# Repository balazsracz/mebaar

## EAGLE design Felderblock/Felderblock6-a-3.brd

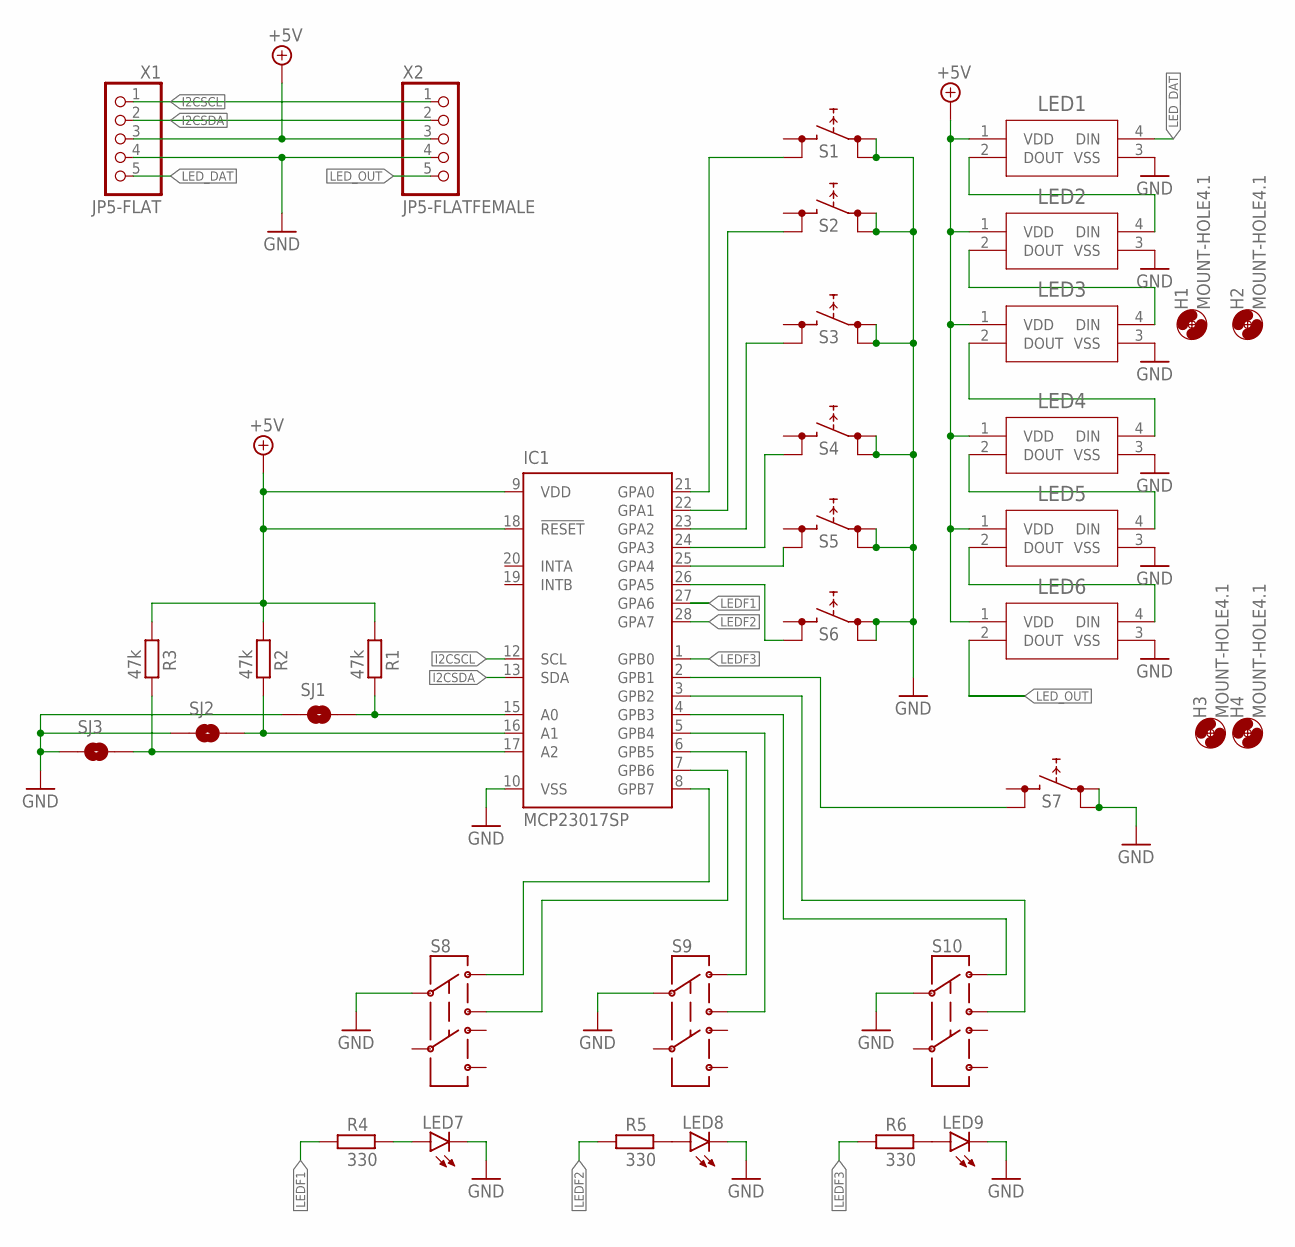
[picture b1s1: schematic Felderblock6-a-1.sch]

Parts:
H1, H2, H3, H4: MOUNT-HOLE4.1; 4,1
IC1: MCP23017SP; DIL28-3
LED1, LED2, LED3, LED4, LED5, LED6: LED-2812BCOM-16347_SPK-M; COM-16347_SPK-M
LED7, LED8, LED9: LEDCHIPLED_0805; CHIPLED_0805
R1, R2, R3: 47k; R0805
R4, R5, R6: 330; R0805
S1, S2, S3, S4, S5, S6, S7: W1; TACTSW-6X6
S8, S9, S10: SWITCH-DPDT; DP-T1
SJ1, SJ2, SJ3: SJRND2; SJ_RND2
X1: JP5-FLAT; JP5F
X2: JP5-FLATFEMALE; JP5F-FEM

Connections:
+5V: IC1.9 (VDD), IC1.18 (!RESET), LED1.1 (VDD), LED2.1 (VDD), LED3.1 (VDD), LED4.1 (VDD), LED5.1 (VDD), LED6.1 (VDD), R1.1, R2.1, R3.1, X1.3, X2.3; also elsewhere on the board
GND: IC1.10 (VSS), LED1.3 (VSS), LED2.3 (VSS), LED3.3 (VSS), LED4.3 (VSS), LED5.3 (VSS), LED6.3 (VSS), LED7.C, LED8.C, LED9.C, S1.1 (1.1), S1.2 (1.2), S2.1 (1.1), S2.2 (1.2), S3.1 (1.1), S3.2 (1.2), S4.1 (1.1), S4.2 (1.2), S5.1 (1.1), S5.2 (1.2), S6.1 (1.1), S6.2 (1.2), S7.1 (1.1), S7.2 (1.2), S8.2 (1C), S9.2 (1C), S10.2 (1C), SJ1.P$1 (1), SJ2.P$1 (1), SJ3.P$1 (1), X1.4, X2.4; also elsewhere on the board
I2CSCL: IC1.12 (SCL), X1.1, X2.1
I2CSDA: IC1.13 (SDA), X1.2, X2.2
LEDF1: IC1.27 (GPA6), R4.1
LEDF2: IC1.28 (GPA7), R5.1
LEDF3: IC1.1 (GPB0), R6.1
LED_DAT: LED1.4 (DIN), X1.5
LED_OUT: LED6.2 (DOUT), X2.5
unnamed 9: IC1.15 (A0), R1.2, SJ1.P$2 (2); also elsewhere on the board
unnamed 10: IC1.16 (A1), R2.2, SJ2.P$2 (2); also elsewhere on the board
unnamed 11: IC1.17 (A2), R3.2, SJ3.P$2 (2); also elsewhere on the board
unnamed: IC1.21 (GPA0), S1.4 (2.2)
unnamed: IC1.22 (GPA1), S2.4 (2.2)
unnamed: IC1.23 (GPA2), S3.4 (2.2)
unnamed: IC1.24 (GPA3), S4.4 (2.2)
unnamed: IC1.25 (GPA4), S5.4 (2.2)
unnamed: IC1.26 (GPA5), S6.4 (2.2)
unnamed: IC1.8 (GPB7), S8.1 (1A)
unnamed: IC1.7 (GPB6), S8.3 (1B)
unnamed: LED1.2 (DOUT), LED2.4 (DIN)
unnamed: LED2.2 (DOUT), LED3.4 (DIN)
unnamed: LED3.2 (DOUT), LED4.4 (DIN)
unnamed: LED4.2 (DOUT), LED5.4 (DIN)
unnamed: LED5.2 (DOUT), LED6.4 (DIN)
unnamed: IC1.6 (GPB5), S9.1 (1A)
unnamed: IC1.5 (GPB4), S9.3 (1B)
unnamed: IC1.4 (GPB3), S10.1 (1A)
unnamed: IC1.3 (GPB2), S10.3 (1B)
unnamed: LED8.A, R5.2
unnamed: LED7.A, R4.2
unnamed: LED9.A, R6.2
unnamed 32: IC1.2 (GPB1), S7.4 (2.2); also elsewhere on the board

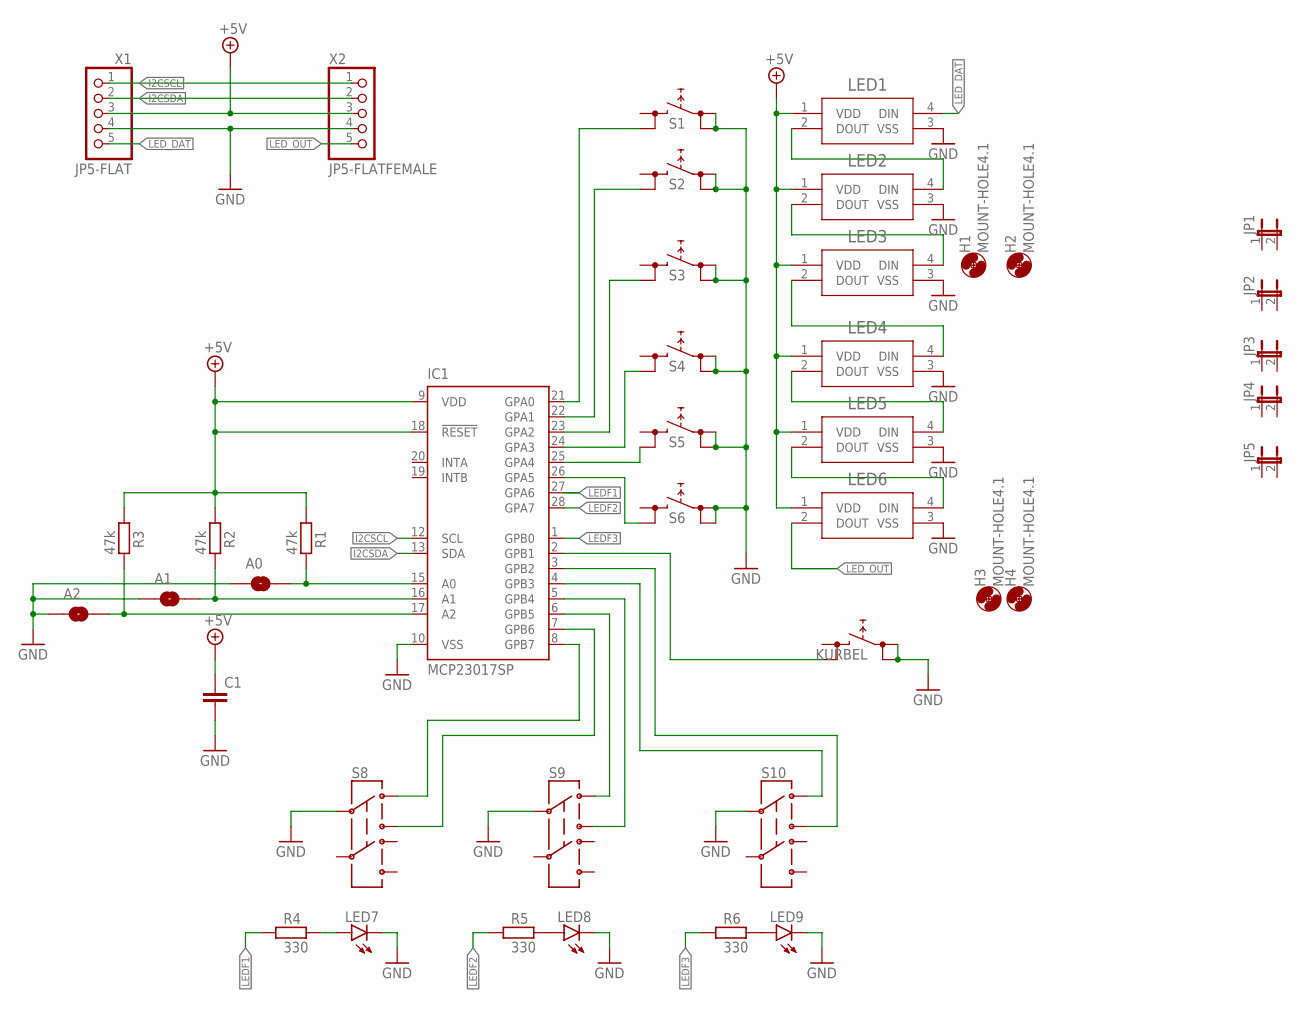
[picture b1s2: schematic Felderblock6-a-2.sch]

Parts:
A0, A1, A2: SJRND2; SJ_RND2
C1: C-EUC0805; C0805
H1, H2, H3, H4: MOUNT-HOLE4.1; 4,1
IC1: MCP23017SP; DIL28-3
JP1, JP2, JP3, JP4, JP5: FELD-BOARD-HOLDER
KURBEL: W1; TACTSW-6X6
LED1, LED2, LED3, LED4, LED5, LED6: LED-2812BCOM-16347_SPK-M; COM-16347_SPK-M
LED7, LED8, LED9: LEDCHIPLED_0805; CHIPLED_0805
R1, R2, R3: 47k; R0805
R4, R5, R6: 330; R0805
S1, S2, S3, S4, S5, S6: W1; TACTSW-6X6
S8, S9, S10: SWITCH-DPDT; DP-T1
X1: JP5-FLAT; JP5F
X2: JP5-FLATFEMALE; JP5F-FEM

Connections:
+5V: C1.1, IC1.9 (VDD), IC1.18 (!RESET), LED1.1 (VDD), LED2.1 (VDD), LED3.1 (VDD), LED4.1 (VDD), LED5.1 (VDD), LED6.1 (VDD), R1.1, R2.1, R3.1, X1.3, X2.3
GND: A0.P$1 (1), A1.P$1 (1), A2.P$1 (1), C1.2, IC1.10 (VSS), KURBEL.1 (1.1), KURBEL.2 (1.2), LED1.3 (VSS), LED2.3 (VSS), LED3.3 (VSS), LED4.3 (VSS), LED5.3 (VSS), LED6.3 (VSS), LED7.C, LED8.C, LED9.C, S1.1 (1.1), S1.2 (1.2), S2.1 (1.1), S2.2 (1.2), S3.1 (1.1), S3.2 (1.2), S4.1 (1.1), S4.2 (1.2), S5.1 (1.1), S5.2 (1.2), S6.1 (1.1), S6.2 (1.2), S8.2 (1C), S9.2 (1C), S10.2 (1C), X1.4, X2.4; also elsewhere on the board
I2CSCL: IC1.12 (SCL), X1.1, X2.1
I2CSDA: IC1.13 (SDA), X1.2, X2.2
LEDF1: IC1.27 (GPA6), R4.1
LEDF2: IC1.28 (GPA7), R5.1
LEDF3: IC1.1 (GPB0), R6.1
LED_DAT: LED1.4 (DIN), X1.5
LED_OUT: LED6.2 (DOUT), X2.5
unnamed 9: A0.P$2 (2), IC1.15 (A0), R1.2; also elsewhere on the board
unnamed 10: A1.P$2 (2), IC1.16 (A1), R2.2; also elsewhere on the board
unnamed 11: A2.P$2 (2), IC1.17 (A2), R3.2; also elsewhere on the board
unnamed: IC1.21 (GPA0), S1.4 (2.2)
unnamed: IC1.22 (GPA1), S2.4 (2.2)
unnamed: IC1.23 (GPA2), S3.4 (2.2)
unnamed: IC1.24 (GPA3), S4.4 (2.2)
unnamed: IC1.25 (GPA4), S5.4 (2.2)
unnamed: IC1.26 (GPA5), S6.4 (2.2)
unnamed: IC1.8 (GPB7), S8.1 (1A)
unnamed: IC1.7 (GPB6), S8.3 (1B)
unnamed: LED1.2 (DOUT), LED2.4 (DIN)
unnamed: LED2.2 (DOUT), LED3.4 (DIN)
unnamed: LED3.2 (DOUT), LED4.4 (DIN)
unnamed: LED4.2 (DOUT), LED5.4 (DIN)
unnamed: LED5.2 (DOUT), LED6.4 (DIN)
unnamed: IC1.6 (GPB5), S9.1 (1A)
unnamed: IC1.5 (GPB4), S9.3 (1B)
unnamed: IC1.4 (GPB3), S10.1 (1A)
unnamed: IC1.3 (GPB2), S10.3 (1B)
unnamed: LED8.A, R5.2
unnamed: LED7.A, R4.2
unnamed: LED9.A, R6.2
unnamed 32: IC1.2 (GPB1), KURBEL.4 (2.2); also elsewhere on the board

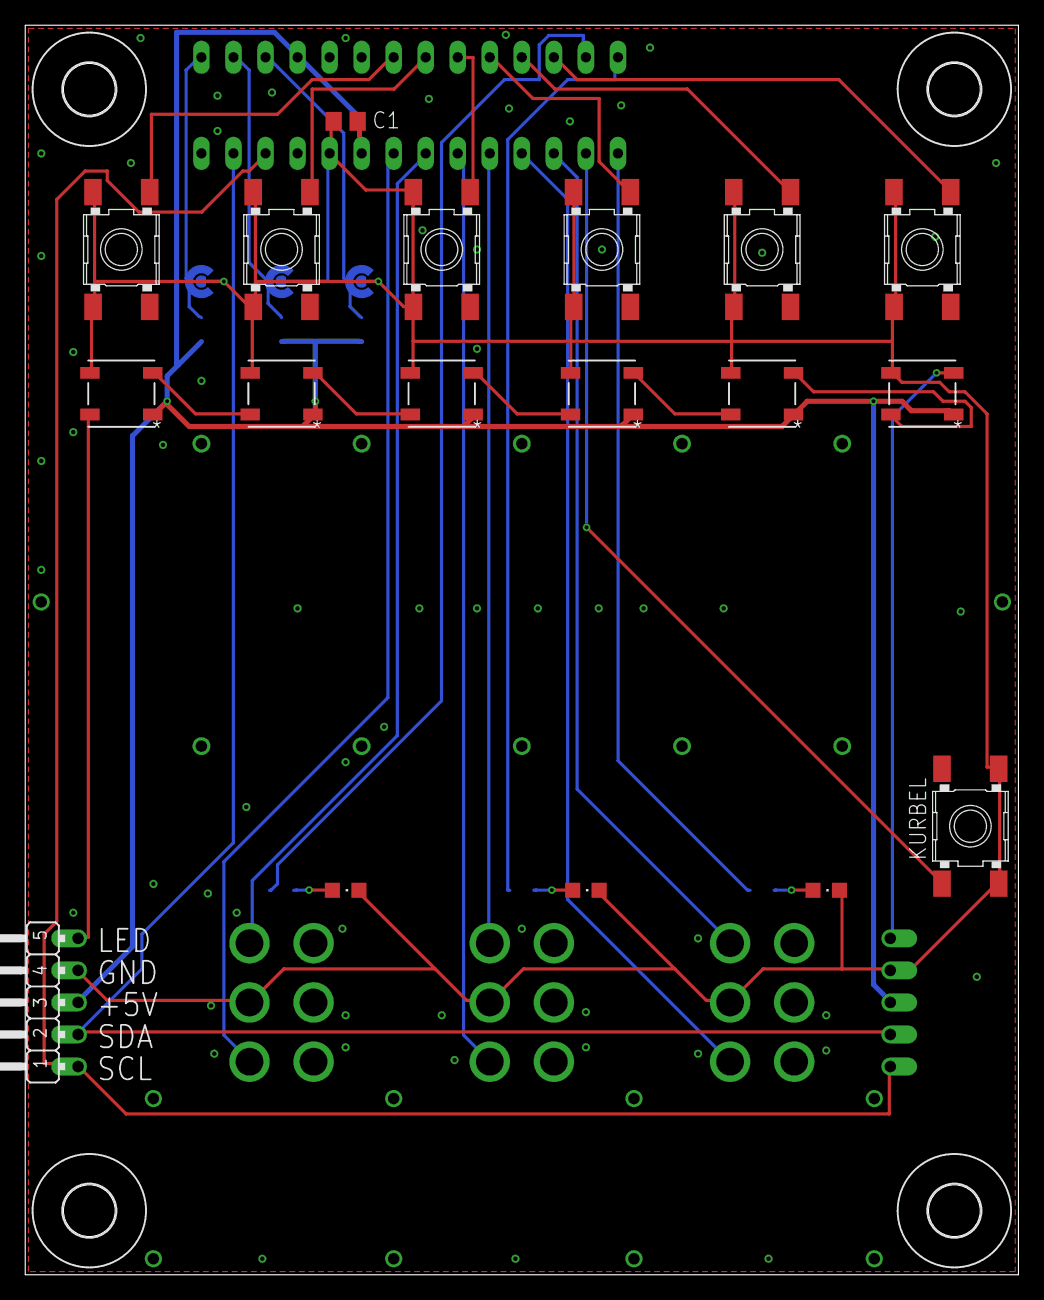
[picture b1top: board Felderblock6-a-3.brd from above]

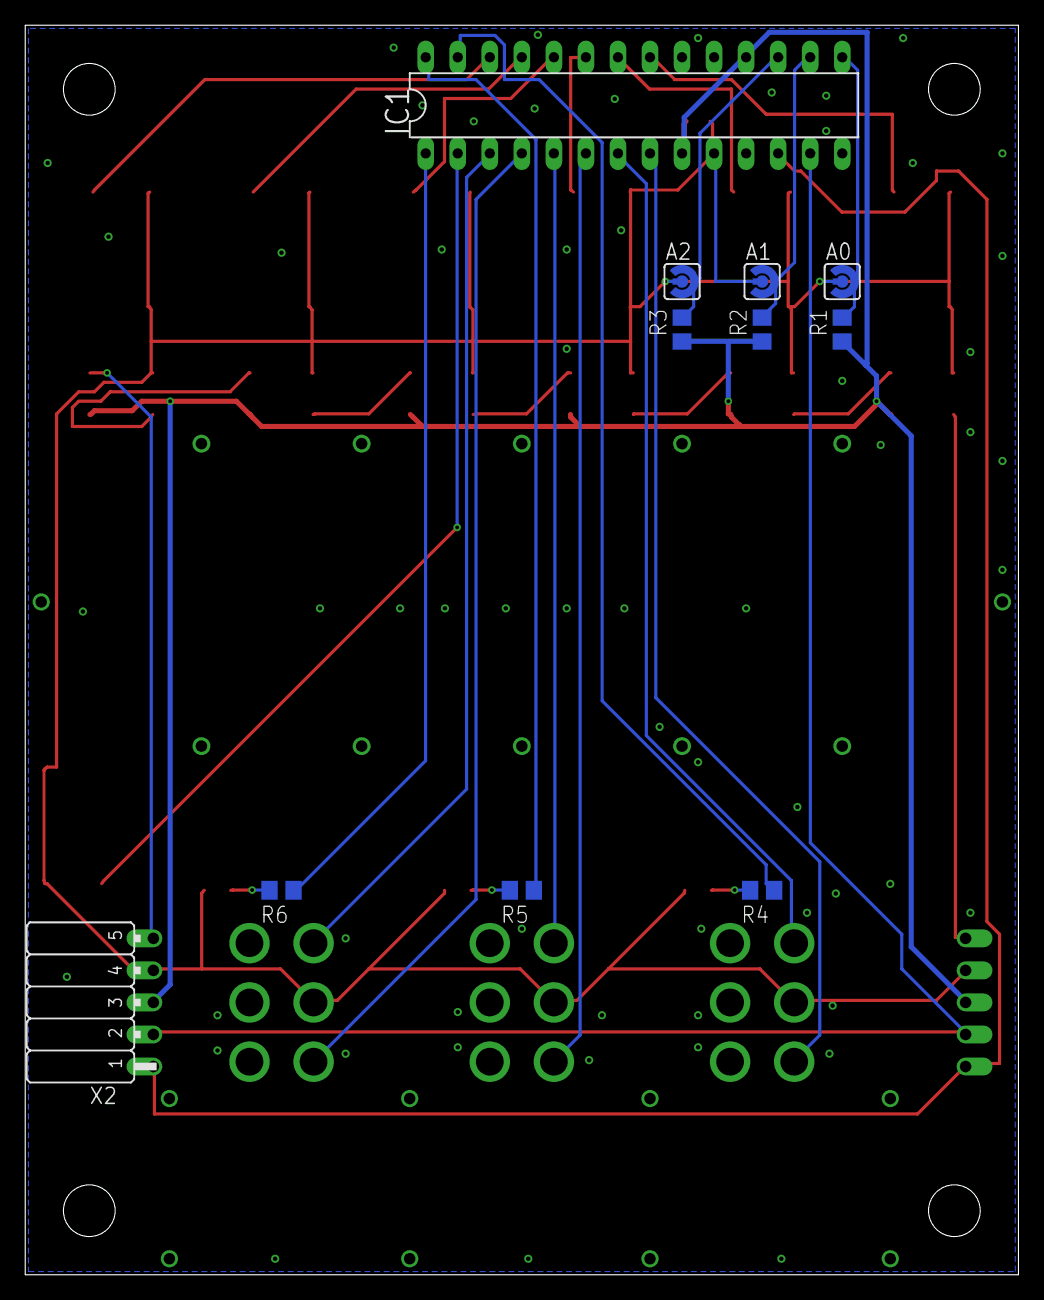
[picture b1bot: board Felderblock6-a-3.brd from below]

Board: 2 copper layers, 78.7 x 99.1 mm, 41 parts (11 on the bottom side), 33 nets.

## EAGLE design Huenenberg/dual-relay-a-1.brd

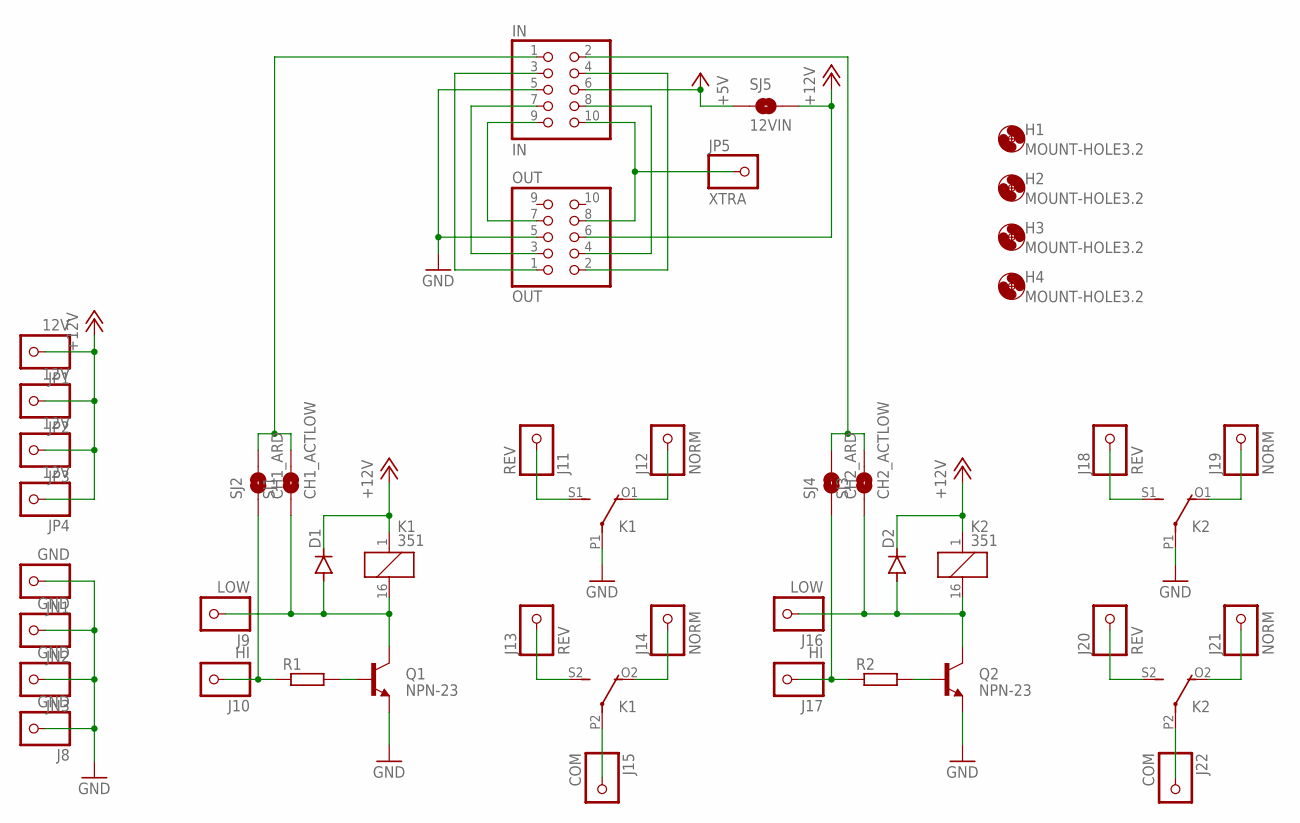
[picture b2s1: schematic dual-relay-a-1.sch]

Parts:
D1, D2: DIODE-MINIMELF; MINIMELF
H1, H2, H3, H4: MOUNT-HOLE3.2; 3,2
IN: IN; CON10M
J8: GND; LARGE-SOLDERPAD
J9, J16: LOW; LARGE-SOLDERPAD
J10, J17: HI; LARGE-SOLDERPAD
J11, J13, J18, J20: REV; LARGE-SOLDERPAD
J12, J14, J19, J21: NORM; LARGE-SOLDERPAD
J15, J22: COM; LARGE-SOLDERPAD
JN1, JN2, JN3: GND; LARGE-SOLDERPAD
JP1, JP2, JP3, JP4: 12V; LARGE-SOLDERPAD
JP5: XTRA; LARGE-SOLDERPAD
K1, K2: 351
OUT: OUT; CON10M
Q1, Q2: NPN-23; SOT23
R1, R2: R-EU_R0805; R0805
SJ1: CH1_ACTLOW; SJ_RND2
SJ2: CH1_ARD; SJ_RND2
SJ3: CH2_ACTLOW; SJ_RND2
SJ4: CH2_ARD; SJ_RND2
SJ5: 12VIN; SJ_RND2

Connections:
+5V: IN.6, SJ5.P$1 (1)
+12V: D1.C, D2.C, JP1.P$1, JP2.P$1, JP3.P$1, JP4.P$1, K1.1, K2.1, OUT.6, SJ5.P$2 (2)
GND: IN.5, K1.P1, K2.P1, OUT.5, Q1.2 (E), Q2.2 (E)
JN4: J8.P$1, JN1.P$1, JN2.P$1, JN3.P$1
unnamed: D1.A, J9.P$1, K1.16 (2), Q1.3 (C), SJ1.P$1 (1)
unnamed: J10.P$1, R1.1, SJ2.P$1 (1)
unnamed: Q1.1 (B), R1.2
unnamed: J11.P$1, K1.S1 (S)
unnamed: J12.P$1, K1.O1 (O)
unnamed: J13.P$1, K1.S2 (S)
unnamed: J14.P$1, K1.O2 (O)
unnamed: J15.P$1, K1.P2
unnamed: D2.A, J16.P$1, K2.16 (2), Q2.3 (C), SJ3.P$1 (1)
unnamed: J17.P$1, R2.1, SJ4.P$1 (1)
unnamed: Q2.1 (B), R2.2
unnamed: J18.P$1, K2.S1 (S)
unnamed: J19.P$1, K2.O1 (O)
unnamed: J20.P$1, K2.S2 (S)
unnamed: J21.P$1, K2.O2 (O)
unnamed: J22.P$1, K2.P2
unnamed: IN.1, SJ1.P$2 (2), SJ2.P$2 (2)
unnamed: IN.2, SJ3.P$2 (2), SJ4.P$2 (2)
unnamed: IN.3, OUT.1
unnamed: IN.7, OUT.3
unnamed: IN.8, OUT.4
unnamed: IN.10, JP5.P$1, OUT.8
unnamed: IN.4, OUT.2
unnamed: IN.9, OUT.7

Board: 2 copper layers, 42 parts (1 on the bottom side), 28 nets, no tracks yet.

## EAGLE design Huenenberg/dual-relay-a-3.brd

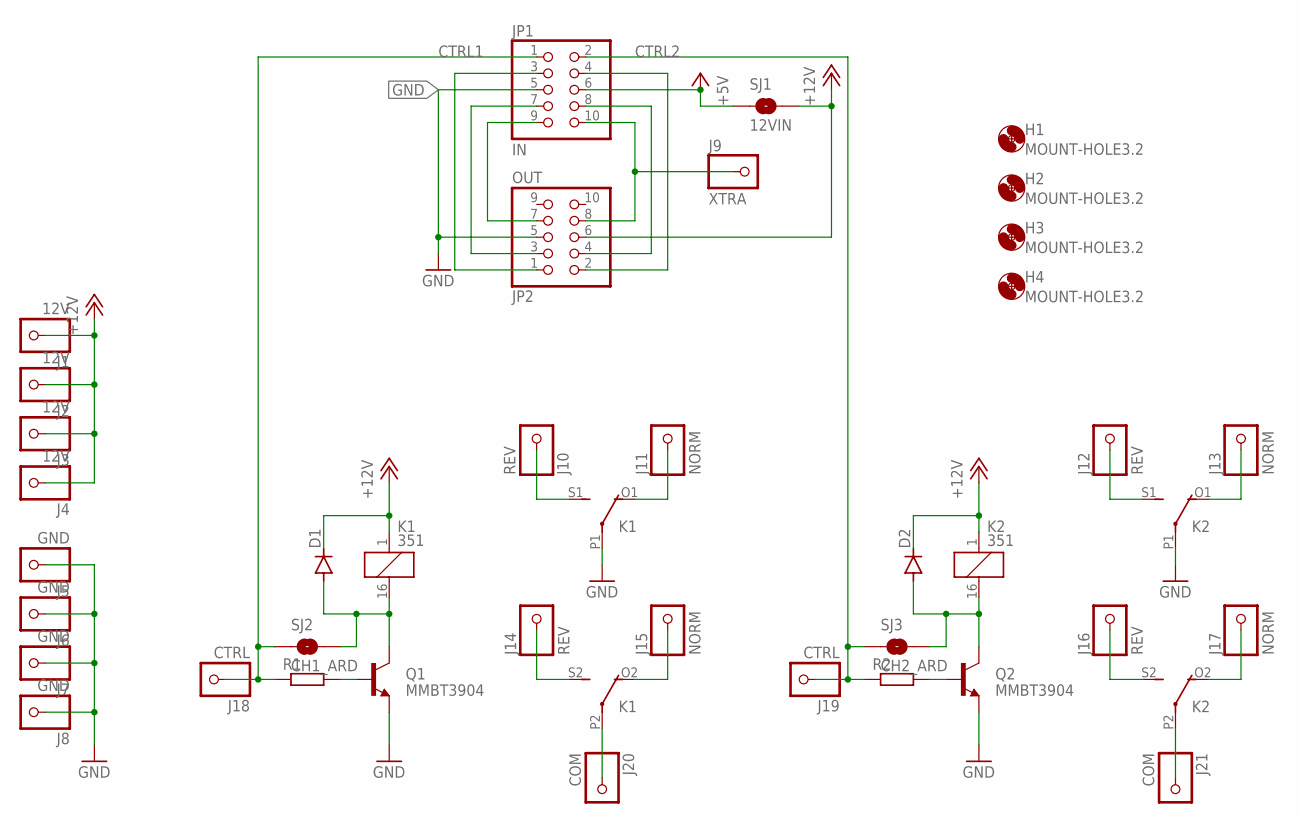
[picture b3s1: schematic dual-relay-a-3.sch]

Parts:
D1, D2: DIODE-MINIMELF; MINIMELF
H1, H2, H3, H4: MOUNT-HOLE3.2; 3,2
J1, J2, J3, J4: 12V; LARGE-SOLDERPAD
J5, J6, J7, J8: GND; LARGE-SOLDERPAD
J9: XTRA; LARGE-SOLDERPAD
J10, J12, J14, J16: REV; LARGE-SOLDERPAD
J11, J13, J15, J17: NORM; LARGE-SOLDERPAD
J18, J19: CTRL; LARGE-SOLDERPAD
J20, J21: COM; LARGE-SOLDERPAD
JP1: IN; CON10M
JP2: OUT; CON10M
K1, K2: 351
Q1, Q2: MMBT3904; SOT23
R1, R2: R-EU_R0805; R0805
SJ1: 12VIN; SJ_RND2
SJ2: CH1_ARD; SJ_RND2
SJ3: CH2_ARD; SJ_RND2

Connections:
+5V: JP1.6, SJ1.P$1 (1)
+12V: D1.C, D2.C, J1.P$1, J2.P$1, J3.P$1, J4.P$1, JP2.6, K1.1, K2.1, SJ1.P$2 (2)
CTRL1: J18.P$1, JP1.1, R1.1, SJ2.P$1 (1)
CTRL2: J19.P$1, JP1.2, R2.1, SJ3.P$1 (1)
GND: J5.P$1, J6.P$1, J7.P$1, J8.P$1, JP1.5, JP2.5, K1.P1, K2.P1, Q1.2 (E), Q2.2 (E)
unnamed: D1.A, K1.16 (2), Q1.3 (C), SJ2.P$2 (2)
unnamed: Q1.1 (B), R1.2
unnamed: J10.P$1, K1.S1 (S)
unnamed: J11.P$1, K1.O1 (O)
unnamed: J14.P$1, K1.S2 (S)
unnamed: J15.P$1, K1.O2 (O)
unnamed: J20.P$1, K1.P2
unnamed: D2.A, K2.16 (2), Q2.3 (C), SJ3.P$2 (2)
unnamed: Q2.1 (B), R2.2
unnamed: J12.P$1, K2.S1 (S)
unnamed: J13.P$1, K2.O1 (O)
unnamed: J16.P$1, K2.S2 (S)
unnamed: J17.P$1, K2.O2 (O)
unnamed: J21.P$1, K2.P2
unnamed: JP1.3, JP2.1
unnamed: JP1.7, JP2.3
unnamed: JP1.8, JP2.4
unnamed: J9.P$1, JP1.10, JP2.8
unnamed: JP1.4, JP2.2
unnamed: JP1.9, JP2.7

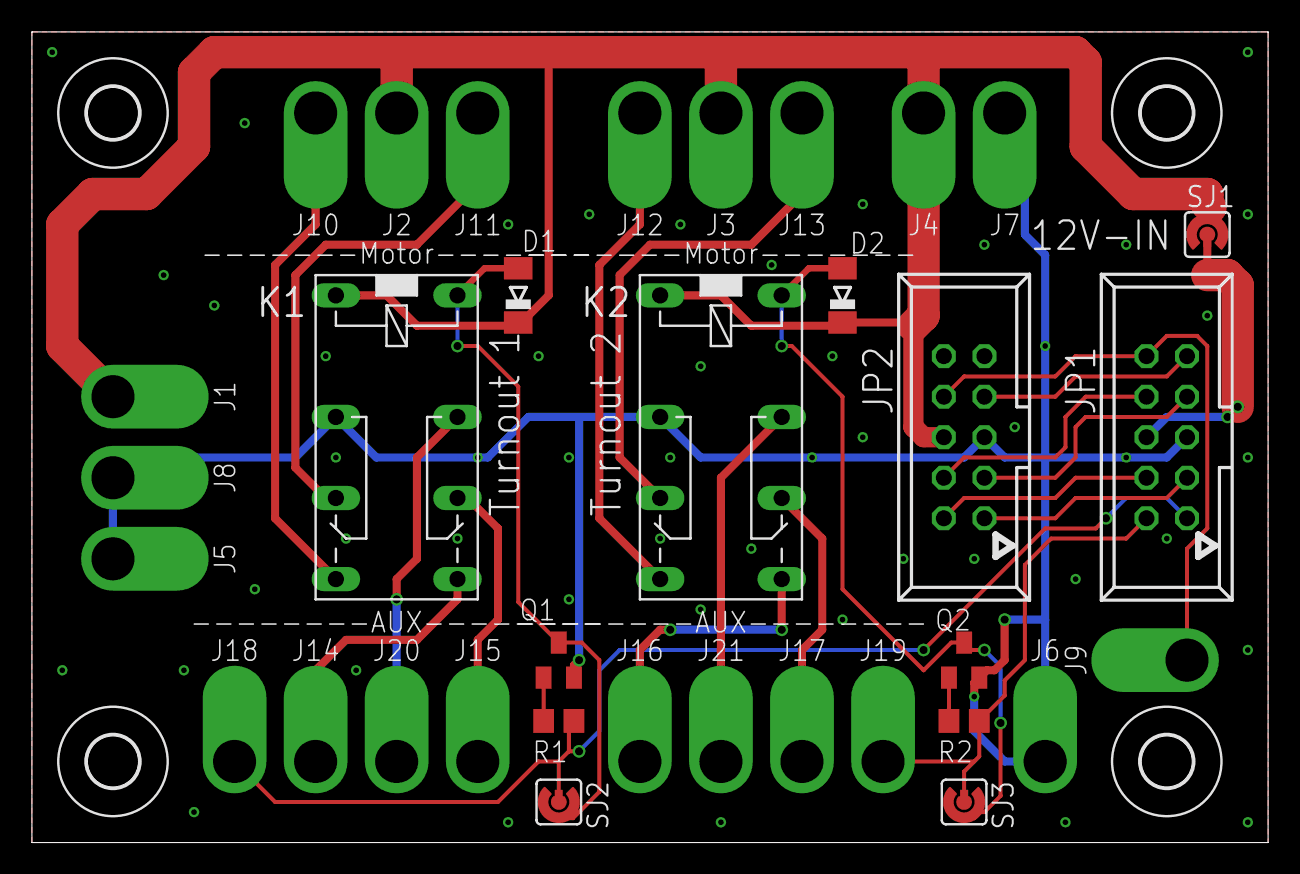
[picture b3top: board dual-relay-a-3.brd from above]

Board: 2 copper layers, 77.5 x 50.8 mm, 38 parts (0 on the bottom side), 25 nets.

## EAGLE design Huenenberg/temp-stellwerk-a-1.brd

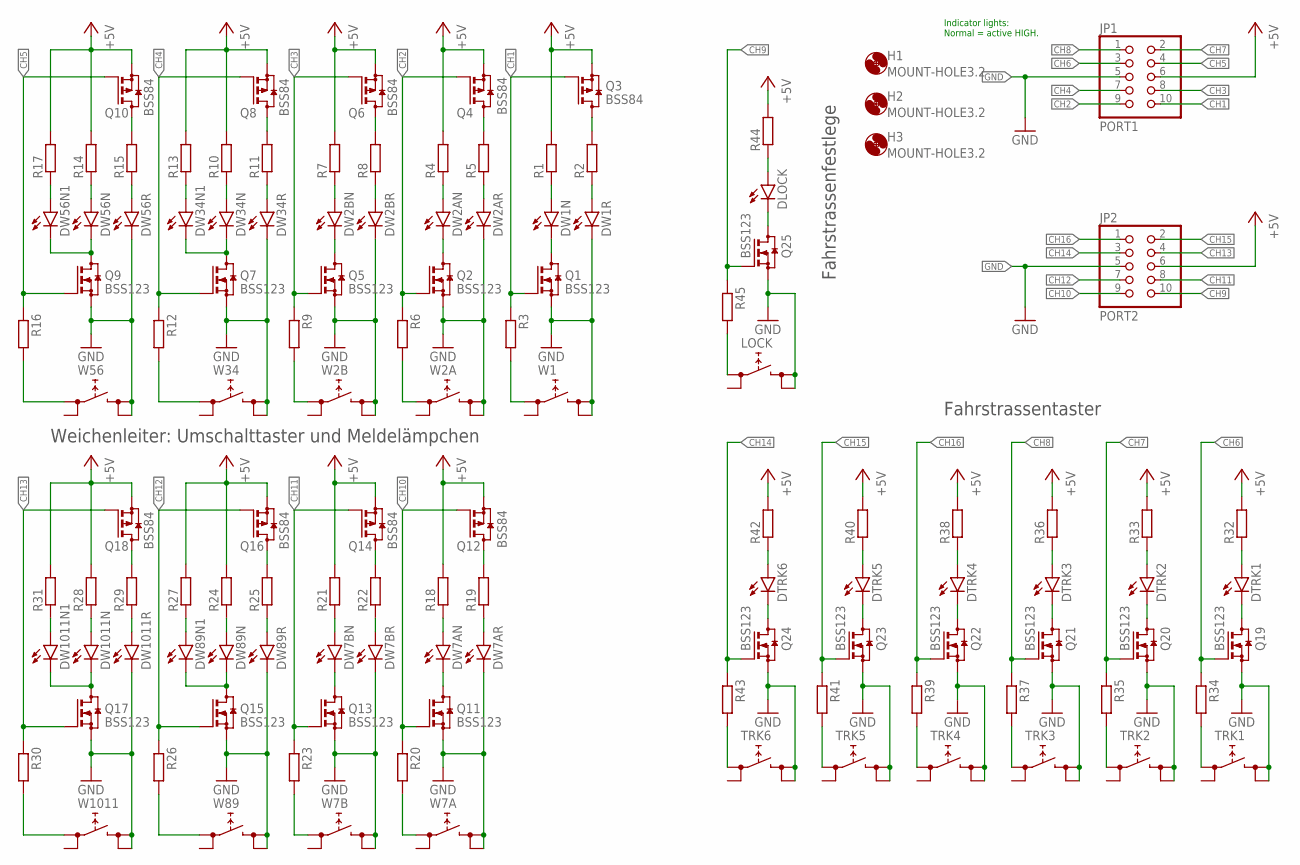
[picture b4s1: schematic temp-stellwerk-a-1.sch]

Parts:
DLOCK: LEDCHIP-LED0805; CHIP-LED0805
DTRK1, DTRK2, DTRK3, DTRK4, DTRK5, DTRK6: LEDCHIP-LED0805; CHIP-LED0805
DW1N, DW1R, DW2AN, DW2AR, DW7AR: LEDCHIP-LED0603; CHIP-LED0603
DW2BN, DW2BR, DW7BN, DW7BR, DW34N, DW34N1, DW34R, DW56N, DW56N1, DW56R, DW89N, DW89N1, DW89R, DW1011N, DW1011N1, DW1011R: LEDCHIP-LED0805; CHIP-LED0805
DW7AN: LEDCHIPLED_0603; CHIPLED_0603
H1, H2, H3: MOUNT-HOLE3.2; 3,2
JP1: PORT1; CON10M
JP2: PORT2; CON10M
LOCK: LOCK; TACTSW-6X6
Q1, Q2, Q5, Q7, Q9, Q11, Q13, Q15, Q17, Q19, Q20, Q21, Q22, Q23, Q24, Q25: BSS123; SOT23
Q3, Q4, Q6, Q8, Q10, Q12, Q14, Q16, Q18: BSS84; SOT23
R1, R2, R3, R4, R5, R6, R7, R8, R9, R10, R11, R12, R13, R14, R15, R16, R17, R18, R19, R20, R21, R22, R23, R24, R25, R26, R27, R28, R29, R30, R31, R32, R33, R34, R35, R36, R37, R38, R39, R40, R41, R42, R43, R44, R45: R-EU_R0805; R0805
TRK1, TRK2, TRK3, TRK4, TRK5, TRK6: TACTSW-6X6S; TACTSW-6X6
W1: W1; TACTSW-6X6
W2A, W2B, W7A, W7B: TACTSW-6X6S; TACTSW-6X6
W34, W56, W89, W1011: XOVER; TACTSW-6X6

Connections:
+5V: JP1.6, JP2.6, Q3.2 (S), Q4.2 (S), Q6.2 (S), Q8.2 (S), Q10.2 (S), Q12.2 (S), Q14.2 (S), Q16.2 (S), Q18.2 (S), R1.2, R4.2, R7.2, R10.2, R13.2, R14.2, R17.2, R18.2, R21.2, R24.2, R27.2, R28.2, R31.2, R32.2, R33.2, R36.2, R38.2, R40.2, R42.2, R44.2
CH1: JP1.10, Q1.1 (G), Q3.1 (G), R3.1
CH2: JP1.9, Q2.1 (G), Q4.1 (G), R6.1
CH3: JP1.8, Q5.1 (G), Q6.1 (G), R9.1
CH4: JP1.7, Q7.1 (G), Q8.1 (G), R12.1
CH5: JP1.4, Q9.1 (G), Q10.1 (G), R16.1
CH6: JP1.3, Q19.1 (G), R34.1
CH7: JP1.2, Q20.1 (G), R35.1
CH8: JP1.1, Q21.1 (G), R37.1
CH9: JP2.10, Q25.1 (G), R45.1
CH10: JP2.9, Q11.1 (G), Q12.1 (G), R20.1
CH11: JP2.8, Q13.1 (G), Q14.1 (G), R23.1
CH12: JP2.7, Q15.1 (G), Q16.1 (G), R26.1
CH13: JP2.4, Q17.1 (G), Q18.1 (G), R30.1
CH14: JP2.3, Q24.1 (G), R43.1
CH15: JP2.2, Q23.1 (G), R41.1
CH16: JP2.1, Q22.1 (G), R39.1
GND: DW1R.C, DW2AR.C, DW2BR.C, DW7AR.C, DW7BR.C, DW34R.C, DW56R.C, DW89R.C, DW1011R.C, JP1.5, JP2.5, LOCK.3 (2.1), LOCK.4 (2.2), Q1.2 (S), Q2.2 (S), Q5.2 (S), Q7.2 (S), Q9.2 (S), Q11.2 (S), Q13.2 (S), Q15.2 (S), Q17.2 (S), Q19.2 (S), Q20.2 (S), Q21.2 (S), Q22.2 (S), Q23.2 (S), Q24.2 (S), Q25.2 (S), TRK1.3 (2.1), TRK1.4 (2.2), TRK2.3 (2.1), TRK2.4 (2.2), TRK3.3 (2.1), TRK3.4 (2.2), TRK4.3 (2.1), TRK4.4 (2.2), TRK5.3 (2.1), TRK5.4 (2.2), TRK6.3 (2.1), TRK6.4 (2.2), W1.3 (2.1), W1.4 (2.2), W2A.3 (2.1), W2A.4 (2.2), W2B.3 (2.1), W2B.4 (2.2), W7A.3 (2.1), W7A.4 (2.2), W7B.3 (2.1), W7B.4 (2.2), W34.3 (2.1), W34.4 (2.2), W56.3 (2.1), W56.4 (2.2), W89.3 (2.1), W89.4 (2.2), W1011.3 (2.1), W1011.4 (2.2)
unnamed: DTRK1.C, Q19.3 (D)
unnamed: DW1N.C, Q1.3 (D)
unnamed: DW1N.A, R1.1
unnamed: DW1R.A, R2.1
unnamed: Q3.3 (D), R2.2
unnamed: DW2AN.C, Q2.3 (D)
unnamed: R3.2, W1.1 (1.1)
unnamed: DW2AN.A, R4.1
unnamed: DW2AR.A, R5.1
unnamed: Q4.3 (D), R5.2
unnamed: R6.2, W2A.1 (1.1)
unnamed: DW2BN.C, Q5.3 (D)
unnamed: DW2BN.A, R7.1
unnamed: DW2BR.A, R8.1
unnamed: Q6.3 (D), R8.2
unnamed: R9.2, W2B.1 (1.1)
unnamed: DW56N.A, R14.1
unnamed: DW34N.A, R10.1
unnamed: DW34R.A, R11.1
unnamed: Q8.3 (D), R11.2
unnamed: R12.2, W34.1 (1.1)
unnamed: DW34N.C, DW34N1.C, Q7.3 (D)
unnamed: DW34N1.A, R13.1
unnamed: DW56R.A, R15.1
unnamed: Q10.3 (D), R15.2
unnamed: R16.2, W56.1 (1.1)
unnamed: DW56N.C, DW56N1.C, Q9.3 (D)
unnamed: DW56N1.A, R17.1
unnamed: DW7AN.C, Q11.3 (D)
unnamed: DW7AN.A, R18.1
unnamed: DW7AR.A, R19.1
unnamed: Q12.3 (D), R19.2
unnamed: R20.2, W7A.1 (1.1)
unnamed: DW7BN.C, Q13.3 (D)
unnamed: DW7BN.A, R21.1
unnamed: DW7BR.A, R22.1
unnamed: Q14.3 (D), R22.2
unnamed: R23.2, W7B.1 (1.1)
unnamed: DW89N.A, R24.1
unnamed: DW89R.A, R25.1
unnamed: Q16.3 (D), R25.2
unnamed: R26.2, W89.1 (1.1)
unnamed: DW89N.C, DW89N1.C, Q15.3 (D)
unnamed: DW89N1.A, R27.1
unnamed: DW1011N.A, R28.1
unnamed: DW1011R.A, R29.1
unnamed: Q18.3 (D), R29.2
unnamed: R30.2, W1011.1 (1.1)
unnamed: DW1011N.C, DW1011N1.C, Q17.3 (D)
unnamed: DW1011N1.A, R31.1
unnamed: DTRK1.A, R32.1
unnamed: DTRK2.C, Q20.3 (D)
unnamed: DTRK2.A, R33.1
unnamed: R34.2, TRK1.1 (1.1)
unnamed: R35.2, TRK2.1 (1.1)
unnamed: DTRK3.C, Q21.3 (D)
unnamed: DTRK3.A, R36.1
unnamed: R37.2, TRK3.1 (1.1)
unnamed: DTRK4.C, Q22.3 (D)
unnamed: DTRK4.A, R38.1
unnamed: R39.2, TRK4.1 (1.1)
unnamed: DTRK5.C, Q23.3 (D)
unnamed: DTRK5.A, R40.1
unnamed: R41.2, TRK5.1 (1.1)
unnamed: DTRK6.C, Q24.3 (D)
unnamed: DTRK6.A, R42.1
unnamed: R43.2, TRK6.1 (1.1)
unnamed: DLOCK.C, Q25.3 (D)
unnamed: DLOCK.A, R44.1
unnamed: LOCK.1 (1.1), R45.2

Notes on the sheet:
Indicator lights: Normal = active HIGH.
Weichenleiter: Umschalttaster und Meldelämpchen
Fahrstrassentaster
Fahrstrassenfestlege

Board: 2 copper layers, 120 parts (70 on the bottom side), 88 nets, no tracks yet.

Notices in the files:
Felderblock/Felderblock6-a-1.sch:
LICENSE: Licensed by the Solderpad Hardware License V2.0
parts and their libraries:
eagleparts: COPYRIGHT: Copyright (C) 2024 Ultra Librarian. All rights reserved.
